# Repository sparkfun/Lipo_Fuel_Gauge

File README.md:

SparkFun LiPo Fuel Gauge - MAX17043
========================================

[*SparkFun LiPo Fuel Gauge (TOL-20680)*](https://www.sparkfun.com/products/20680)

LiPo batteries are a great way to power your projects. They're small, lightweight, and pack a good punch for their size. Unfortunately, even the best batteries eventually run low on power, and when they do it's often unexpected (and at the worst time). Don't be caught by surprise next time your board suddenly powers down! 

The SparkFun LiPo Fuel Gauge connects your battery to your project and uses a sophisticated algorithm to detect the relative state of charge and direct A/D measurement of battery voltage. In other words, it tells your microcontroller how much 'fuel' is left in the tank. The LiPo Fuel Gauge communicates with your project over I<sup>2</sup>C and an alert pin also tells you when the charge has dropped below a certain percentage.

Repository Contents
-------------------

* **/Firmware** - Example C code 
* **/Hardware** - Eagle design files (.brd, .sch)
* **/Production** - Production panel files (.brd)

Documentation
--------------
* **[Particle Photon Library](https://github.com/sparkfun/SparkFun_MAX17043_Particle_Library)** - Particle Library for the MAX17043 that is used in the [SparkFun Photon Battery Shield](https://www.sparkfun.com/products/13626).
* **[Arduino Project Example](https://learn.sparkfun.com/tutorials/wireless-joystick-hookup-guide#MAX17043)** - Arduino project example that uses the MAX17043 in the [Wireless Joystick Kit](https://www.sparkfun.com/products/14051).
* **[SparkFun Arduino Library](https://github.com/sparkfun/SparkFun_MAX1704x_Fuel_Gauge_Arduino_Library)** - SparkFun Arduino library
* **[Arduino Library](https://github.com/porrey/max1704x)** - Arduino library from user "porrey." This is another Arduino library that is available. 
* **SparkFun Fritzing repo** - Fritzing diagrams for SparkFun products.
  * **[TOL-20680](https://github.com/sparkfun/Fritzing_Parts/blob/main/products/20680_sfe_lipo_fuel_gauge_MAX17043_MAX1704X.fzpz)**
  * **[TOL-10617](https://github.com/sparkfun/Fritzing_Parts/blob/main/products/10617_sfe_lipo_fuel_gauge.fzpz)**
* **[SparkFun 3D Model repo](https://github.com/sparkfun/3D_Models)** - 3D models of SparkFun products.
* **[Hookup Guide](https://learn.sparkfun.com/tutorials/2946)** - Basic hookup guide for the MAX17043 and MAX17048.

Product Versions
----------------
* [TOL-20680](https://www.sparkfun.com/products/20680) - v1.2
* [TOL-10617](https://www.sparkfun.com/products/10617) - Initial Release, v1.1

License Information
-------------------
This product is _**open source**_! 

The **hardware** is released under [Creative Commons ShareAlike 4.0 International](https://creativecommons.org/licenses/by-sa/4.0/).

The **code** is beerware; if you see me (or any other SparkFun employee) at the local, and you've found our code helpful, please buy us a round!

Please use, reuse, and modify these files as you see fit. Please maintain attribution to SparkFun Electronics and release anything derivative under the same license.

Distributed as-is; no warranty is given.

- Your friends at SparkFun.

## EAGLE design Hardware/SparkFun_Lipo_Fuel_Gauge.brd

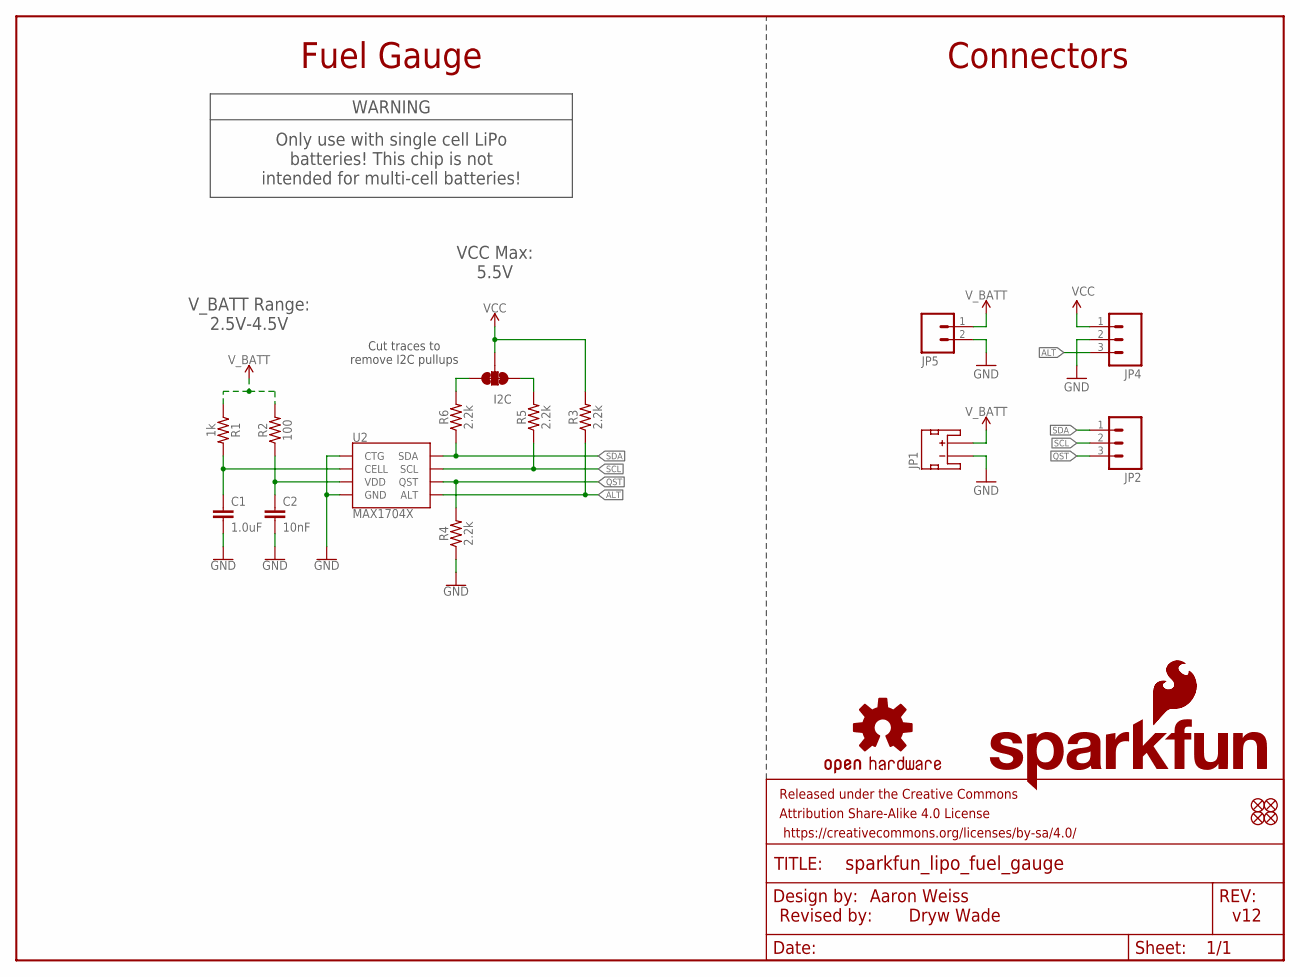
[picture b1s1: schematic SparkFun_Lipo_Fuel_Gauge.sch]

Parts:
C1: 1.0uF; 0402-TIGHT
C2: 10nF; 0402-TIGHT
FRAME1: FRAME-LETTER; CREATIVE_COMMONS
I2C: JUMPER-SMT_3_2-NC_TRACE_SILK; SMT-JUMPER_3_2-NC_TRACE_SILK
JP1: input; JST-2-SMD
JP2, JP4: CONN_031X03_NO_SILK; 1X03_NO_SILK
JP3: SFE_LOGO_FLAME.1_INCH; SFE_LOGO_FLAME_.1
JP5: CONN_021X02_NO_SILK; 1X02_NO_SILK
JP6, JP7, JP8, JP9: FIDUCIALUFIDUCIAL; FIDUCIAL-MICRO
LOGO1: SFE_LOGO_NAME_FLAMEBLANK; BLANK
R1: 1k; 0402-TIGHT
R2: 100; 0402-TIGHT
R3, R4, R5, R6: 2.2k; 0402-TIGHT
U2: MAX1704X; TDFN-8
U$1: OSHW-LOGOS; OSHW-LOGO-S

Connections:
ALT: JP4.3, R3.1, U2.5 (ALT)
GND: C1.2, C2.2, JP1.1 (-), JP4.2, JP5.2, R4.1, U2.1 (CTG), U2.4 (GND), U2.EP (GND)
unnamed: I2C.3, R6.2
unnamed: C1.1, R1.2, U2.2 (CELL)
unnamed: I2C.1, R5.2
QST: JP2.3, R4.2, U2.6 (QST)
SCL: JP2.2, R5.1, U2.7 (SCL)
SDA: JP2.1, R6.1, U2.8 (SDA)
VCC: I2C.2, JP4.1, R3.2
VDD: C2.1, R2.1, U2.3 (VDD)
V_BATT: JP1.2 (+), JP5.1, R1.1, R2.2

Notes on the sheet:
v12
Aaron Weiss
Revised by:
Dryw Wade
Connectors
Fuel Gauge
WARNING
Only use with single cell LiPo batteries! This chip is not intended for multi-cell batteries!
V_BATT Range: 2.5V-4.5V
VCC Max: 5.5V
Cut traces to remove I2C pullups

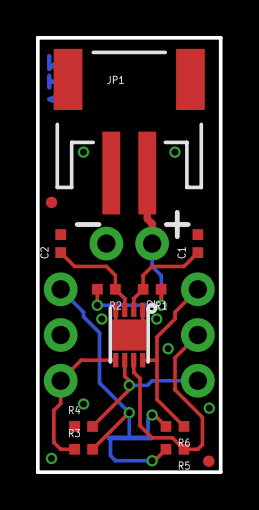
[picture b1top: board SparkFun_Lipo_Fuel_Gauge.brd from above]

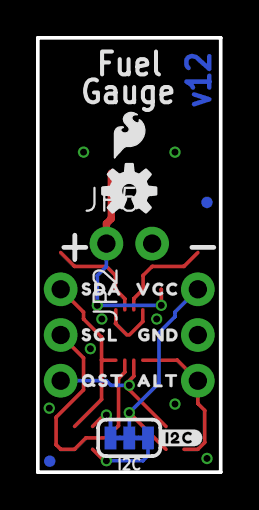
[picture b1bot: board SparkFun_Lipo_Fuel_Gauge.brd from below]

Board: 2 copper layers, 10.2 x 24.1 mm, 29 parts (15 on the bottom side), 11 nets.

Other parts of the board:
U$2: SDA0
U$3: SCL0
U$4: QST0
U$5: VCC0
U$6: GND0
U$7: ALT0
U$8: #I2C#0

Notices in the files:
parts and their libraries:
SparkFun-Aesthetics: Licensing: Creative Commons ShareAlike 4.0 International - https://creativecommons.org/licenses/by-sa/4.0
SparkFun-Aesthetics: Released under the Creative Commons Attribution Share-Alike 4.0 License
SparkFun-Aesthetics: Released under the Creative Commons
